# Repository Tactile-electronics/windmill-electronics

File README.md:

I can't work out how to do the two circuits on one board with the connections that you can add and remove.  So I've made two separate boards.  

I wanted you to have alook before I wire it up on Kicad as at the moment I'm not sure if I've got it right and some connections seem wrong

e.g the connections out of the board that is in series  have been connected together on the pcb - by KICAD - do I need  to change it in the schematic or can I do that in the wiring?

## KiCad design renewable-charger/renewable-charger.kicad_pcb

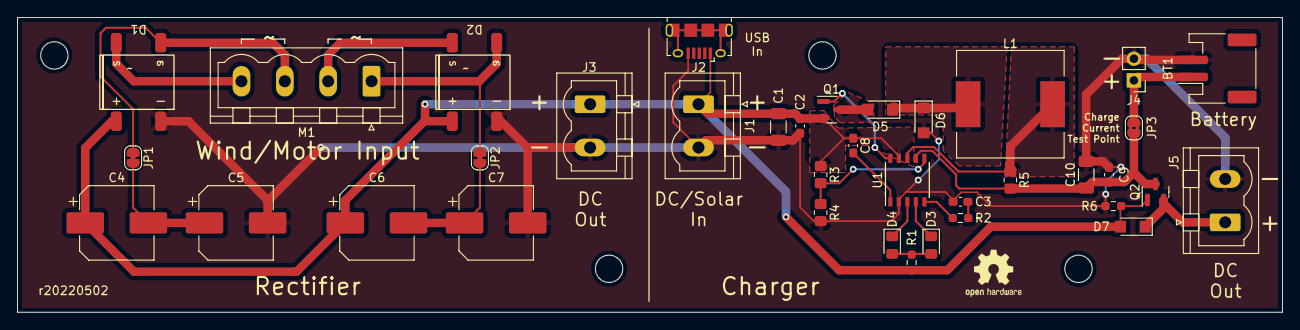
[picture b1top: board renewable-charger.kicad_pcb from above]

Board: 2 copper layers, 148.2 x 34.5 mm, 37 parts (0 on the bottom side), 22 nets.

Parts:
BT1: Battery_Cell; JST_PH_S2B-PH-SM4-TB_1x02-1MP_P2.00mm_Horizontal
C1, C10: 10uF 50V; C_1206_3216Metric_Pad1.33x1.80mm_HandSolder
C2, C9: 1uF; C_0603_1608Metric_Pad1.08x0.95mm_HandSolder
C3: 220nF; C_0603_1608Metric_Pad1.08x0.95mm_HandSolder
C4, C5, C6, C7: C_Polarized_Small; CP_Elec_8x10.5
C8: 0.1uF; C_0603_1608Metric_Pad1.08x0.95mm_HandSolder
D1, D2: D_Bridge_+-AA; BridgeRectifier_DBLS
D3: LED Green; LED_0805_2012Metric_Pad1.15x1.40mm_HandSolder
D4: LED Red; LED_0805_2012Metric_Pad1.15x1.40mm_HandSolder
D5, D6, D7: D_Schottky; D_SMF
J1: Solar Input; PhoenixContact_MSTBVA_2,5_2-G-5,08_1x02_P5.08mm_Vertical
J2: USB_B_Micro; USB_Micro-B_Amphenol_10118194_Horizontal
J3: Wind Output; PhoenixContact_MSTBVA_2,5_2-G-5,08_1x02_P5.08mm_Vertical
J4: Battery; PinHeader_1x02_P2.54mm_Vertical
J5: Output; PhoenixContact_MSTBVA_2,5_2-G-5,08_1x02_P5.08mm_Vertical
JP1, JP2: SolderJumper_2_Bridged; SolderJumper-2_P1.3mm_Bridged_RoundedPad1.0x1.5mm
JP3: Test Point; SolderJumper-2_P1.3mm_Bridged2Bar_RoundedPad1.0x1.5mm
L1: 100uH 2.5A; L_12x12mm_H6mm
M1: Stepper_Motor_bipolar; PhoenixContact_MSTBVA_2,5_4-G-5,08_1x04_P5.08mm_Vertical
Q1, Q2: P-channel 30V 4A MOSfet; SOT-23
R1, R6: R_Small; R_0603_1608Metric_Pad0.98x0.95mm_HandSolder
R2: 120R; R_0603_1608Metric_Pad0.98x0.95mm_HandSolder
R3, R4: R_Small; R_0805_2012Metric_Pad1.20x1.40mm_HandSolder
R5: Rcs; R_0805_2012Metric_Pad1.20x1.40mm_HandSolder
U1: CN3791; SSOP-10_3.9x4.9mm_P1.00mm

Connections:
/Power +: C1.1, C2.1, C4.1, C6.1, C8.1, D1.1 (+), D2.1 (+), D7.2 (A), J1.1, J2.1 (VBUS), J3.1, Q1.2 (S), Q2.1 (G), R1.1, R3.1, R6.1, U1.9 (VCC)
/Power -: BT1.2 (-), C1.2, C2.2, C3.2, C5.2, C7.2, C9.2, C10.2, D1.2 (-), D2.2 (-), D6.2 (A), J1.2, J2.5 (GND), J3.2, J4.2, J5.2, R4.2, R6.2, U1.2 (GND)
unnamed: BT1.1 (+), J4.1, JP3.2 (B)
unnamed: C3.1, R2.2
unnamed: D1.3, M1.4
unnamed: D3.2 (A), D4.2 (A), R1.2
unnamed: D3.1 (K), U1.4 (DONE)
unnamed: D4.1 (K), U1.3 (CHRG)
unnamed: D5.2 (A), Q1.3 (D)
unnamed: D5.1 (K), D6.1 (K), L1.1
unnamed: D7.1 (K), J5.1, Q2.2 (S)
unnamed: D1.4, JP1.1 (A), M1.3
unnamed: C4.2, C5.1, JP1.2 (B)
unnamed: D2.4, JP2.1 (A), M1.1
unnamed: C6.2, C7.1, JP2.2 (B)
unnamed: C9.1, C10.1, JP3.1 (A), Q2.3 (D), R5.2, U1.7 (BAT)
unnamed: D2.3, M1.2 (-)
unnamed: Q1.1 (G), U1.10 (DRV)
unnamed: R2.1, U1.5 (COM)
unnamed: L1.2, R5.1, U1.8 (CSP)
unnamed: R3.2, R4.1, U1.6 (MPPT)
unnamed: C8.2, U1.1 (VG)

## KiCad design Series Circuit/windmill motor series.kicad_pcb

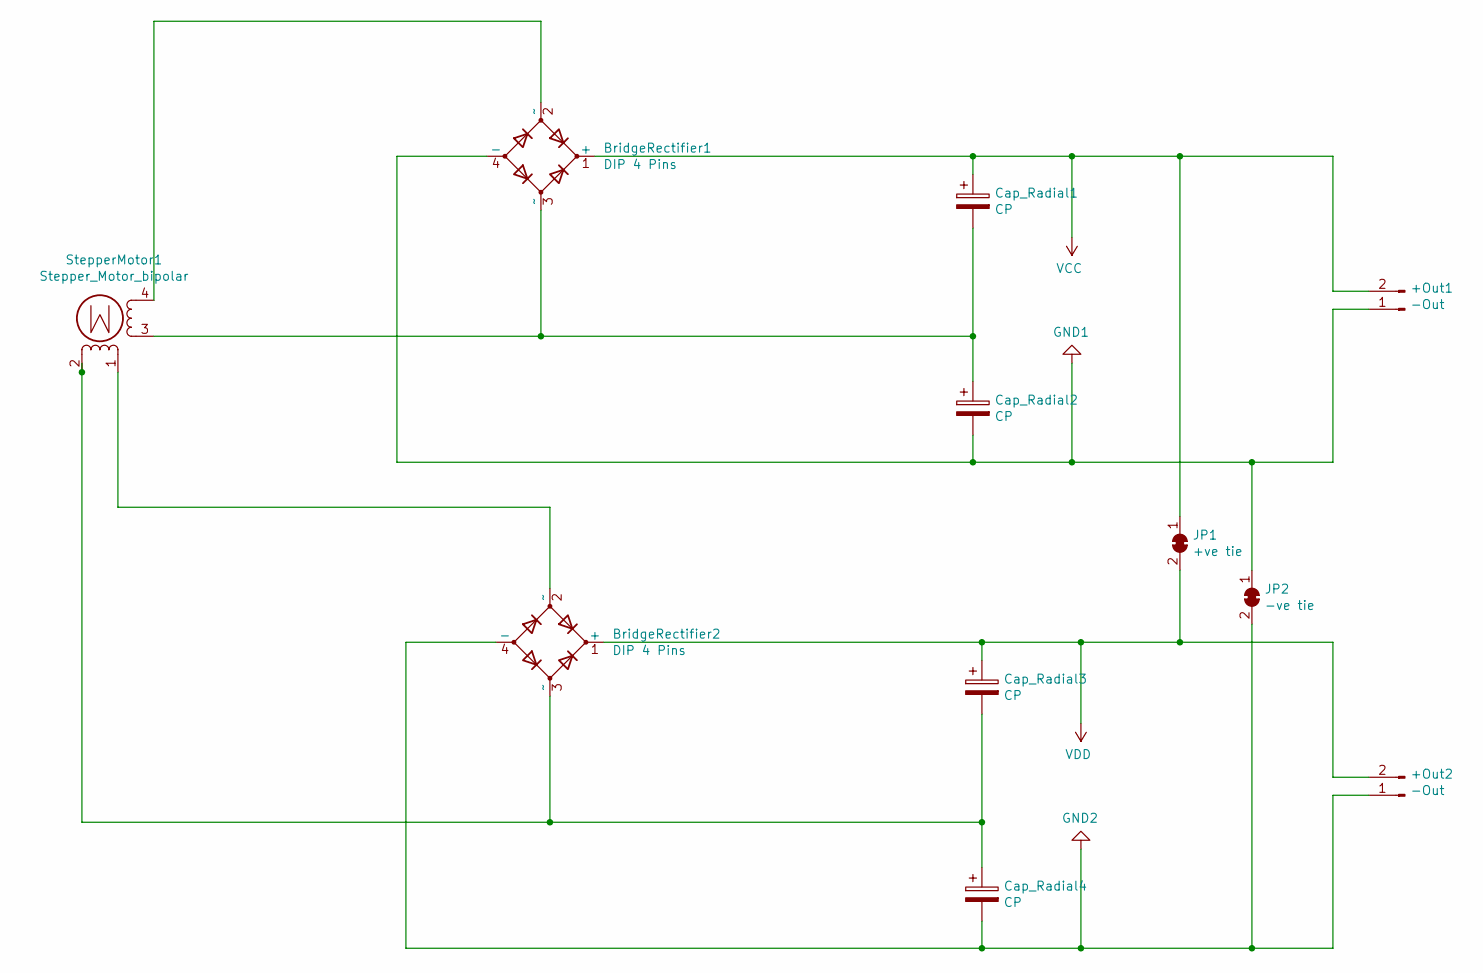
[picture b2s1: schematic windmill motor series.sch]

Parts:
+Out1, +Out2: -Out; WAGO_734_2pin_Straight_RuggedPads
BridgeRectifier1, BridgeRectifier2: DIP 4 Pins; Diode_Bridge_DIP-4_W7.62mm_P5.08mm
Cap_Radial1, Cap_Radial2, Cap_Radial3, Cap_Radial4: CP; CP_Radial_Tantal_D8.0mm_P5.00mm
JP1: +ve tie; SolderJumper-2_P1.3mm_Bridged_RoundedPad1.0x1.5mm
JP2: -ve tie; SolderJumper-2_P1.3mm_Bridged_RoundedPad1.0x1.5mm
StepperMotor1: Stepper_Motor_bipolar; TE_MATE-N-LOK_350211-1_1x04_P5.08mm_Vertical

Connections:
GND1: +Out1.1, BridgeRectifier1.4 (-), Cap_Radial2.2, JP2.1 (A)
GND2: +Out2.1, BridgeRectifier2.4 (-), Cap_Radial4.2, JP2.2 (B)
unnamed: BridgeRectifier1.2 (~~), StepperMotor1.4
unnamed: BridgeRectifier1.3 (~~), Cap_Radial1.2, Cap_Radial2.1, StepperMotor1.3
unnamed: BridgeRectifier2.2 (~~), StepperMotor1.1
unnamed: BridgeRectifier2.3 (~~), Cap_Radial3.2, Cap_Radial4.1, StepperMotor1.2 (-)
VCC: +Out1.2, BridgeRectifier1.1 (+), Cap_Radial1.1, JP1.1 (A)
VDD: +Out2.2, BridgeRectifier2.1 (+), Cap_Radial3.1, JP1.2 (B)

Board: 2 copper layers, 11 parts (0 on the bottom side), 8 nets, no tracks yet.

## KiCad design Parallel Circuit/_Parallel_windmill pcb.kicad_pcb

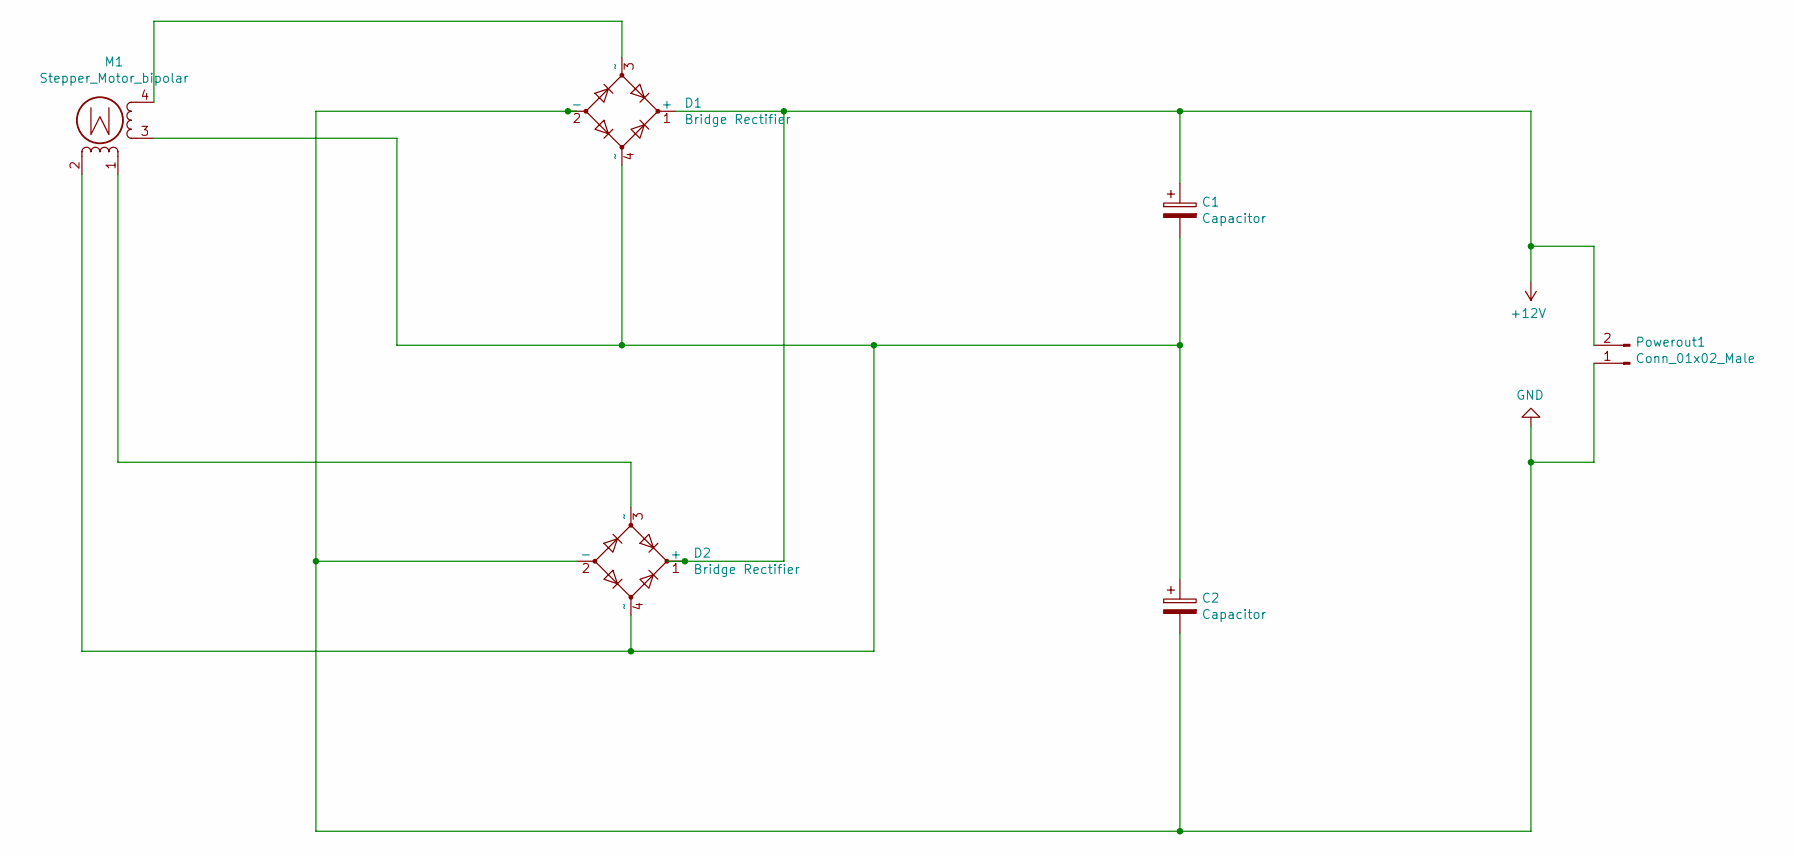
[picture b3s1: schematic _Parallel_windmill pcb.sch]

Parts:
C1, C2: Capacitor; CP_Radial_D8.0mm_P5.00mm
D1, D2: Bridge Rectifier; Diode_Bridge_DIP-4_W7.62mm_P5.08mm
M1: Stepper_Motor_bipolar; TE_MATE-N-LOK_350211-1_1x04_P5.08mm_Vertical
Powerout1: Conn_01x02_Male; WAGO_734_2pin_Straight_RuggedPads

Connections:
+12V: C1.1, D1.1 (+), D2.1 (+), Powerout1.2
GND: C2.2, D1.2 (-), D2.2 (-), Powerout1.1
unnamed: C1.2, C2.1, D1.4 (~~), D2.4 (~~), M1.2 (-), M1.3
unnamed: D1.3 (~~), M1.4
unnamed: D2.3 (~~), M1.1

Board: 2 copper layers, 6 parts (0 on the bottom side), 5 nets, no tracks yet.

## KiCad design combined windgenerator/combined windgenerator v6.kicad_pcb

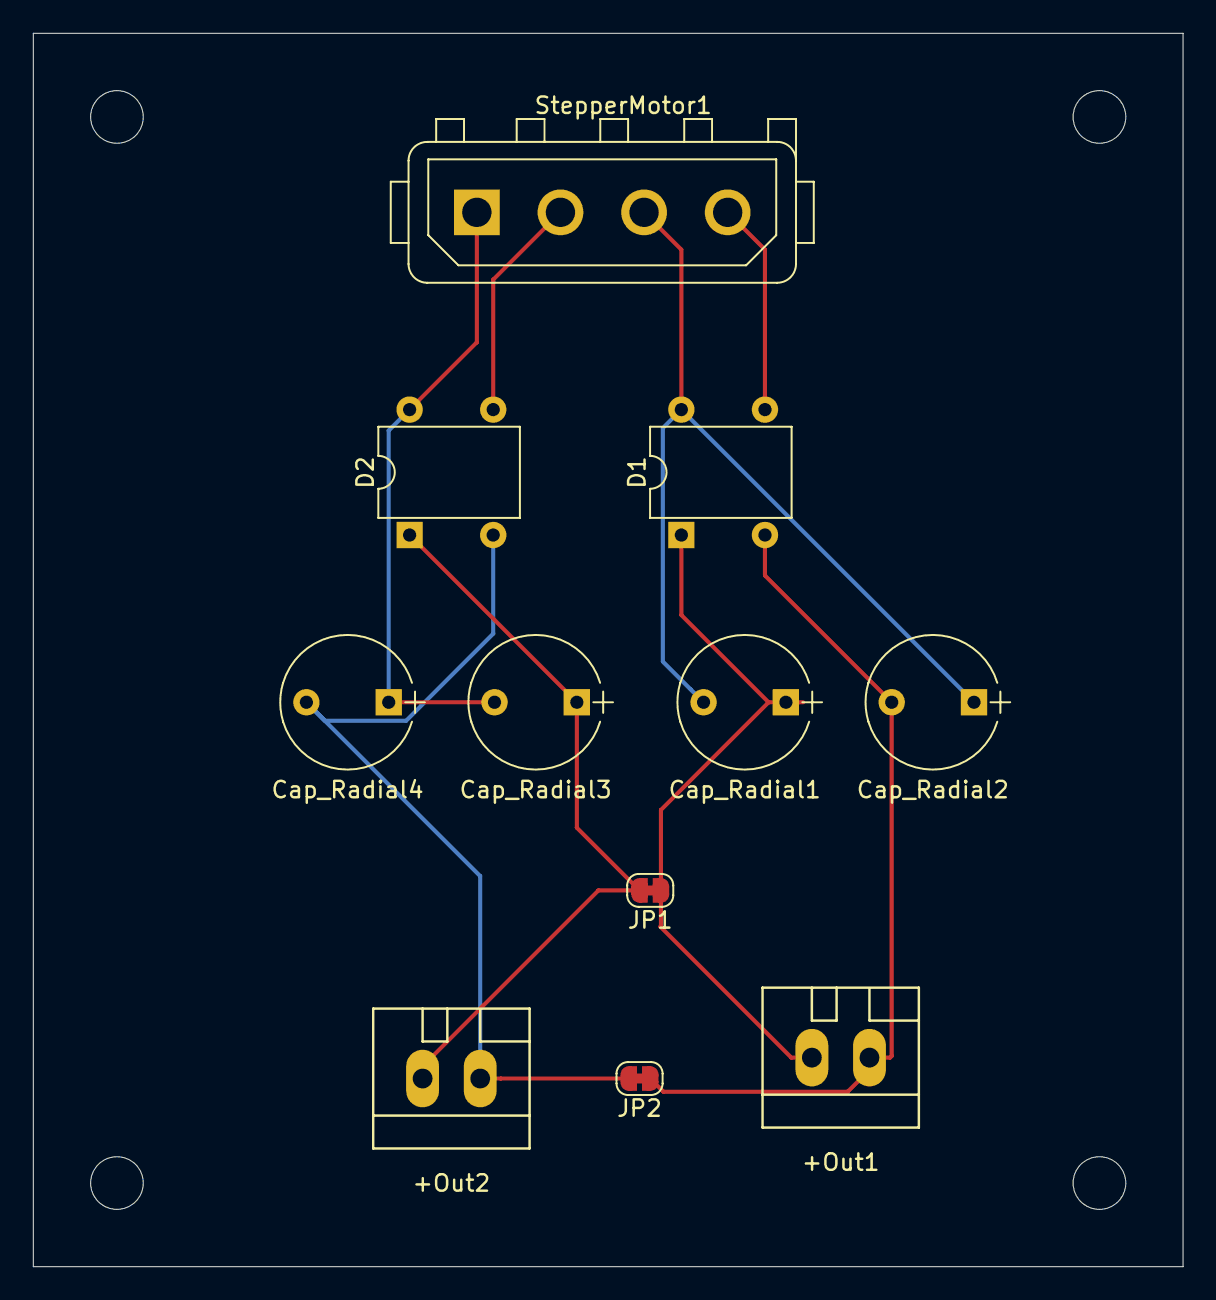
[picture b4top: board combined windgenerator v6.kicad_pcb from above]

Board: 2 copper layers, 69.8 x 74.9 mm, 11 parts (0 on the bottom side), 8 nets.

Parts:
+Out1, +Out2: -Out; WAGO_734_2pin_Straight_RuggedPads
Cap_Radial1, Cap_Radial2, Cap_Radial3, Cap_Radial4: CP; CP_Radial_Tantal_D8.0mm_P5.00mm
D1, D2: D_Bridge_+-AA; Diode_Bridge_DIP-4_W7.62mm_P5.08mm
JP1: +ve tie; SolderJumper-2_P1.3mm_Bridged_RoundedPad1.0x1.5mm
JP2: -ve tie; SolderJumper-2_P1.3mm_Bridged_RoundedPad1.0x1.5mm
StepperMotor1: Stepper_Motor_bipolar; TE_MATE-N-LOK_350211-1_1x04_P5.08mm_Vertical

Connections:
Earth: +Out2.1, Cap_Radial4.2, D2.2, JP2.2
GND: +Out1.1, Cap_Radial2.2, D1.2, JP2.1
unnamed: Cap_Radial1.2, Cap_Radial2.1, D1.4, StepperMotor1.3
unnamed: Cap_Radial3.2, Cap_Radial4.1, D2.4, StepperMotor1.1
unnamed: D1.3, StepperMotor1.4
unnamed: D2.3, StepperMotor1.2
VCC: +Out1.2, Cap_Radial1.1, D1.1, JP1.1
VDD: +Out2.2, Cap_Radial3.1, D2.1, JP1.2

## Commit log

2021-07-27 Create pcb design
2021-07-27 Create info
2021-07-28 Separate out power flags and add jumpers to allow tied operation.
2021-07-30 Create final pcb
2021-07-30 Create pcb
2021-08-01 Create pcbs
2022-02-20 Initial work on the charger schematic. Components and mosfet still needed. Part of #2
2022-03-21 Schematic almost finished—most components chosen with part numbers. Start made on PCB. Part of #2
2022-03-28 Add windmill rectifying voltage-doubler circuit to the schematic. Part of #6
2022-03-30 The windmill rectifier circuit is laid out on the PCB, apart from routing bits to the output connector, as its final location isn't set yet. Part of #6
2022-04-03 Tweaks to the rectifier circuit. Part of #6
2022-04-03 Add test point to measure current into the battery. Implements #8
2022-04-03 Add micro-USB connector for USB charging. Implements #7
2022-04-04 Disconnect battery output when charging; add through-hole battery connector alternative. Part of #5
2022-04-23 Reduce power trace thickness
2022-04-24 All connections wired on PCB. Still needs zones, final position for mounting holes and edges, and some labelling. Part of #4
2022-04-24 Added copper zones; positioned mounting holes and tidied up edge cuts. Just labels left. Part of #4
2022-05-02 Silkscreen additions for labelling, revision number, etc. added. Final part of #4
